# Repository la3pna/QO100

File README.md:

View this project on [CADLAB.io](https://cadlab.io/project/2009). 

# QO100
QO-100 / Eshail upconverter 2.4GHz.

Please use the cadlab link above to see the PCB and schematics.

# todo
Commit interdigital filter design
Preformance data
Graphs
LO design

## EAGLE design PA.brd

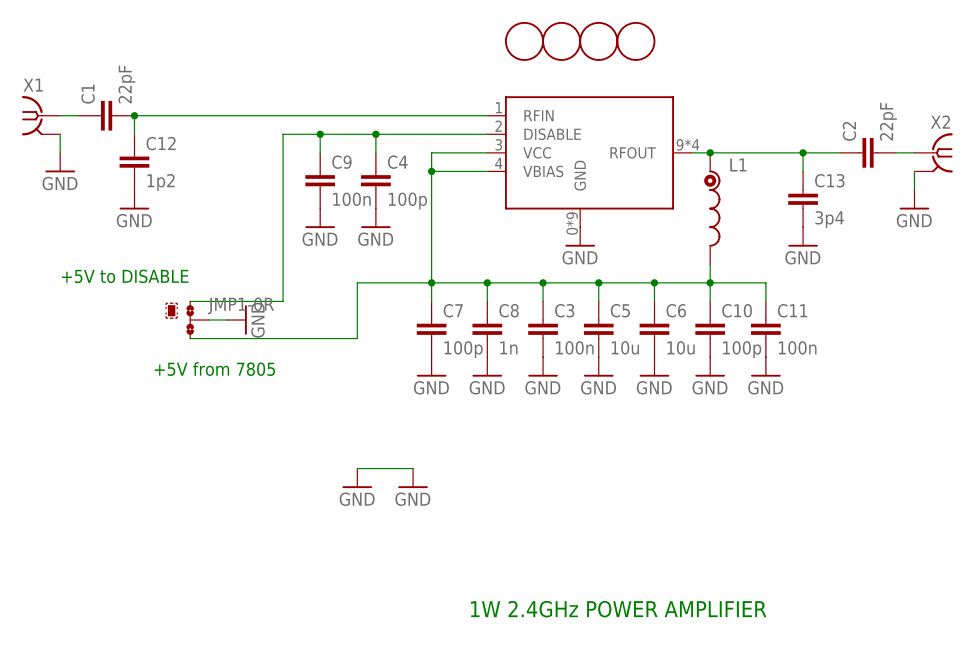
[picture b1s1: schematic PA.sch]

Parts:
C1, C2: 22pF; C0603
C3, C9, C11: 100n; C0603
C4, C7, C10: 100p; C0603
C5, C6: 10u; C1210
C8: 1n; C0603
C12: 1p2; C0603
C13: 3p4; C0603
JMP1: 0R-JUMPB; B0R-JMP
L1: INDUCTOR0603; 0603
U$1: ADL5606; LFCSP-16-4X4
U$2, U$3, U$4, U$5: FIDUCIAL; FIDUCIAL_1MM
X1, X2: SMA-142-0711-821/826; J502-ND-142-0711-821/826

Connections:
GND: C3.2, C4.2, C5.2, C6.2, C7.2, C8.2, C9.2, C10.2, C11.2, C12.2, C13.2, JMP1.2, U$1.0 (GND), U$1.5 (GND), U$1.6 (GND), U$1.7 (GND), U$1.8 (GND), U$1.13 (GND), U$1.14 (GND), U$1.15 (GND), U$1.16 (GND), X1.G@1 (2), X1.G@2 (2), X1.G@3 (2), X1.G@4 (2), X2.G@1 (2), X2.G@2 (2), X2.G@3 (2), X2.G@4 (2)
unnamed: C1.1, X1.1
unnamed: C2.1, C13.1, L1.1, U$1.9 (RFOUT), U$1.10 (RFOUT), U$1.11 (RFOUT), U$1.12 (RFOUT)
unnamed: C4.1, C9.1, JMP1.1, U$1.2 (DISABLE)
unnamed: C3.1, C5.1, C6.1, C7.1, C8.1, C10.1, C11.1, JMP1.3, L1.2, U$1.3 (VCC), U$1.4 (VBIAS)
unnamed: C2.2, X2.1
unnamed: C1.2, C12.1, U$1.1 (RFIN)

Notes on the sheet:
+5V from 7805
+5V to DISABLE
1W 2.4GHz POWER AMPLIFIER

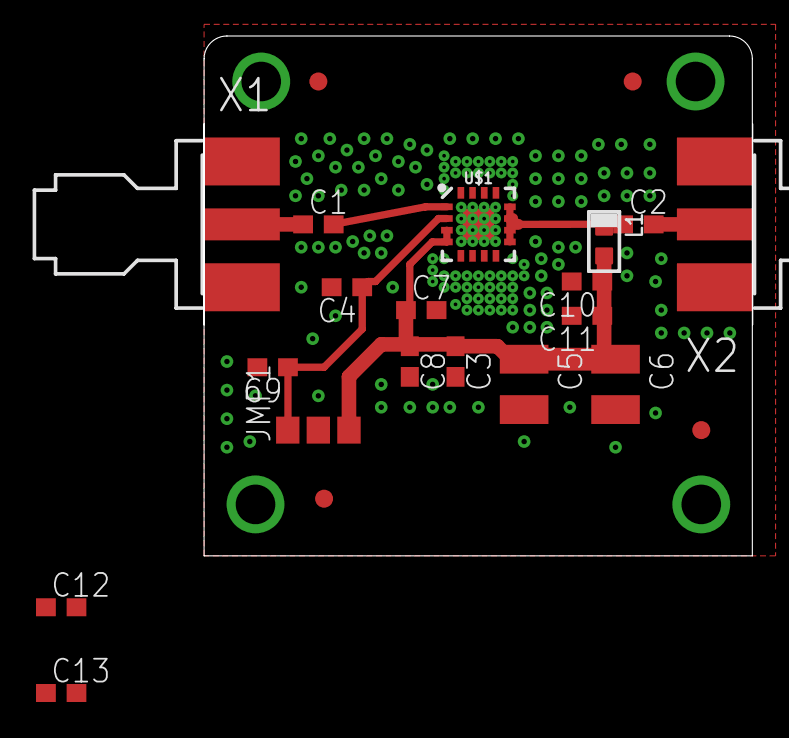
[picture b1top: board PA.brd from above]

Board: 2 copper layers, 30.5 x 28.9 mm, 22 parts (0 on the bottom side), 7 nets.

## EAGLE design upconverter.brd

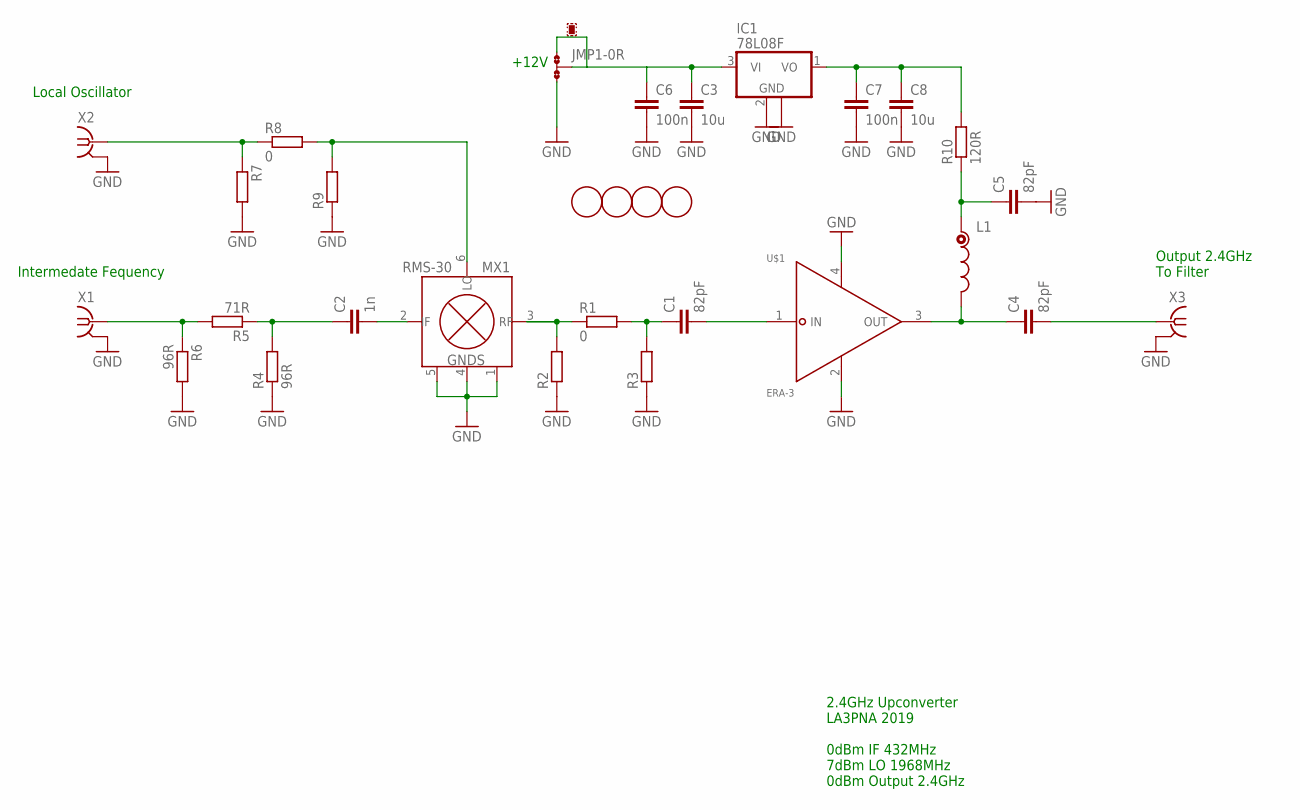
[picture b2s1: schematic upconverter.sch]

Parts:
C1, C5: 82pF; C0603K
C2: 1n; C0603K
C3, C8: 10u; C1210
C4: 82pF; C0805
C6, C7: 100n; C0603K
IC1: 78L08F; SOT89
JMP1: 0R-JUMPA; A0R-JMP
L1: INDUCTOR0603; 0603
MX1: RMS-30; CD636
R1, R8: 0; R1005
R2, R3, R7, R9: R-EU_R1005; R1005
R4, R6: 96R; R1005
R5: 71R; R1005
R10: 120R; R1206
U$1: ERA-3; MAR4SM
U$2, U$3, U$4, U$5: FIDUCIAL; FIDUCIAL_1MM
X1, X2, X3: SMA-142-0711-821/826; J502-ND-142-0711-821/826

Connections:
GND: C3.2, C5.2, C6.2, C7.2, C8.2, IC1.2 (GND), IC1.2@1 (GND), JMP1.3, MX1.1 (GND), MX1.4 (GND), MX1.5 (GND), R2.1, R3.1, R4.1, R6.2, R7.2, R9.1, U$1.2, U$1.4, X1.G@1 (2), X1.G@2 (2), X1.G@3 (2), X1.G@4 (2), X2.G@1 (2), X2.G@2 (2), X2.G@3 (2), X2.G@4 (2), X3.G@1 (2), X3.G@2 (2), X3.G@3 (2), X3.G@4 (2)
unnamed: C2.1, R4.2, R5.1
unnamed: R5.2, R6.1, X1.1
unnamed: C2.2, MX1.2 (IF)
unnamed: C4.1, L1.2, U$1.3 (OUT)
unnamed: C1.2, U$1.1 (IN)
unnamed: C1.1, R1.2, R3.2
unnamed: MX1.3 (RF), R1.1, R2.2
unnamed: R7.1, R8.1, X2.1
unnamed: MX1.6 (LO), R8.2, R9.2
unnamed: C5.1, L1.1, R10.1
unnamed: C4.2, X3.1
unnamed: C7.1, C8.1, IC1.1 (VO), R10.2
unnamed: C3.1, C6.1, IC1.3 (VI), JMP1.1, JMP1.2

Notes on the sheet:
+12V
2.4GHz Upconverter LA3PNA 2019 0dBm IF 432MHz 7dBm LO 1968MHz 0dBm Output 2.4GHz
Local Oscillator
Intermedate Fequency
Output 2.4GHz To Filter

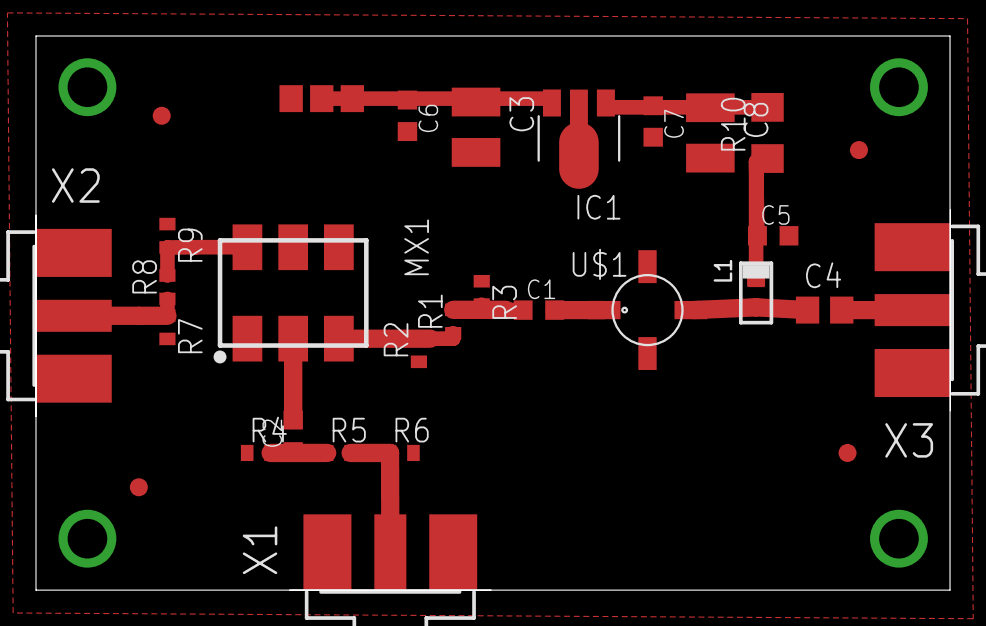
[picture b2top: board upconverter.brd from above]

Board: 2 copper layers, 50.8 x 30.8 mm, 30 parts (0 on the bottom side), 14 nets.

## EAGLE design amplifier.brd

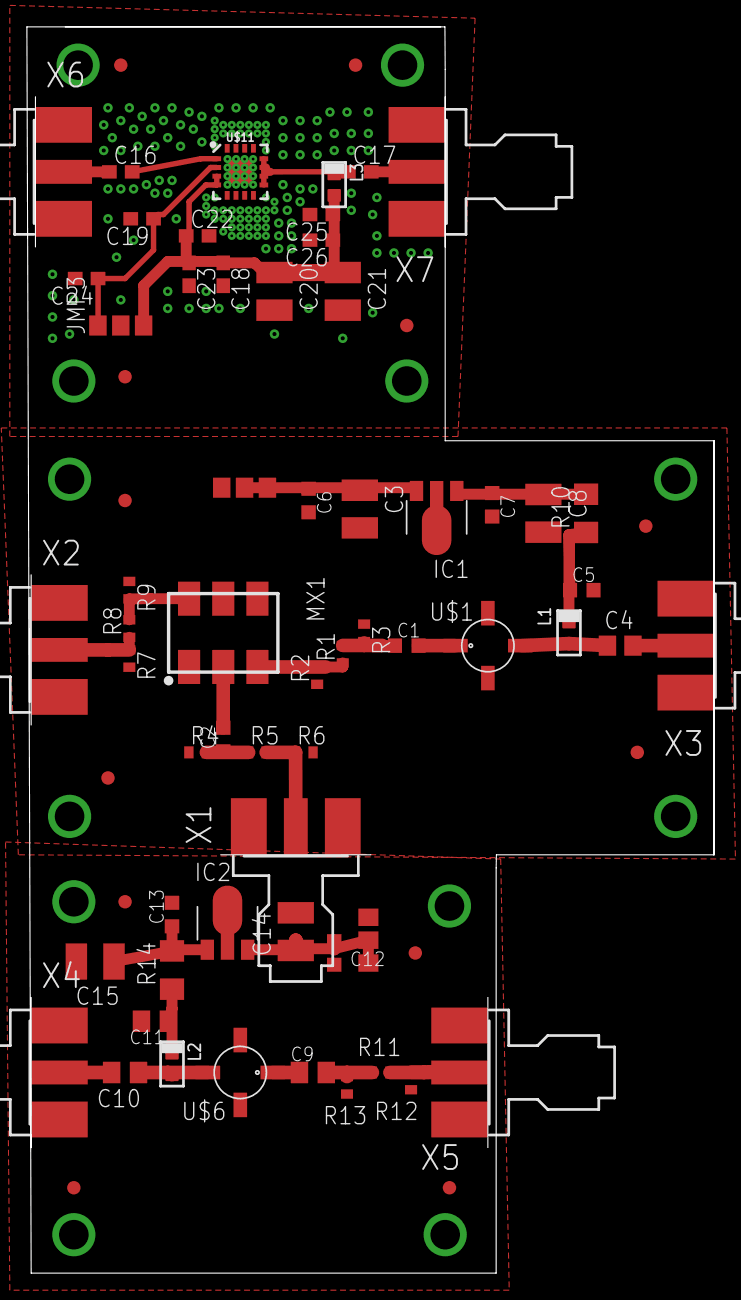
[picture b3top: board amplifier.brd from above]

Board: 2 copper layers, 51.1 x 92.7 mm, 71 parts (0 on the bottom side), 30 nets.

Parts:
C1, C2, C5, C6, C7, C12, C13: C0603K
C3, C8, C14, C15: C1210
C4: C0805
C9, C10, C11: C0805K
C16, C17: C0603
C18, C24, C26: 100n; C0603
C19, C22, C25: 100p; C0603
C20, C21: 10u; C1210
C23: 1n; C0603
IC1, IC2: 78L08F; SOT89
JMP1, JMP2: 0R-JUMPA; A0R-JMP
JMP3: 0R-JUMPB; B0R-JMP
L1, L2, L3: 0603
MX1: ADE-1; CD636
R1, R2, R3, R4, R5, R6, R7, R8, R9, R11, R12, R13: R1005
R10, R14: R1206
U$1, U$6: ERA; MAR4SM
U$2, U$3, U$4, U$5, U$7, U$8, U$9, U$10, U$12, U$13, U$14, U$15: FIDUCIAL; FIDUCIAL_1MM
U$11: ADL5606; LFCSP-16-4X4
X1, X2, X3, X4, X5, X6, X7: J502-ND-142-0711-821/826

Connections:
GND: C11.2, C12.2, C13.2, C14.2, C15.2, IC2.2, IC2.2@1, JMP2.3, R12.1, R13.1, U$6.2, U$6.4, X4.G@1, X4.G@2, X4.G@3, X4.G@4, X5.G@1, X5.G@2, X5.G@3, X5.G@4
GND1: C3.2, C5.2, C6.2, C7.2, C8.2, IC1.2, IC1.2@1, JMP1.3, MX1.1, MX1.4, MX1.5, R2.1, R3.1, R4.1, R6.2, R7.2, R9.1, U$1.2, U$1.4, X1.G@1, X1.G@2, X1.G@3, X1.G@4, X2.G@1, X2.G@2, X2.G@3, X2.G@4, X3.G@1, X3.G@2, X3.G@3, X3.G@4
GND2: C18.2, C19.2, C20.2, C21.2, C22.2, C23.2, C24.2, C25.2, C26.2, JMP3.2, U$11.0, U$11.5, U$11.6, U$11.7, U$11.8, U$11.13, U$11.14, U$11.15, U$11.16, X6.G@1, X6.G@2, X6.G@3, X6.G@4, X7.G@1, X7.G@2, X7.G@3, X7.G@4
unnamed: C2.1, R4.2, R5.1
unnamed: R5.2, R6.1, X1.1
unnamed: C2.2, MX1.2
unnamed: C4.1, L1.2, U$1.3
unnamed: C1.2, U$1.1
unnamed: C1.1, R1.2, R3.2
unnamed: MX1.3, R1.1, R2.2
unnamed: R7.1, R8.1, X2.1
unnamed: MX1.6, R8.2, R9.2
unnamed: C5.1, L1.1, R10.1
unnamed: C4.2, X3.1
unnamed: C7.1, C8.1, IC1.1, R10.2
unnamed: C3.1, C6.1, IC1.3, JMP1.1, JMP1.2
unnamed: C10.1, L2.2, U$6.3
unnamed: C9.2, U$6.1
unnamed: C9.1, R11.2, R13.2
unnamed: R11.1, R12.2, X5.1
unnamed: C11.1, L2.1, R14.1
unnamed: C10.2, X4.1
unnamed: C13.1, C15.1, IC2.1, R14.2
unnamed: C12.1, C14.1, IC2.3, JMP2.1, JMP2.2
unnamed: C19.1, C24.1, JMP3.1, U$11.2
unnamed: C18.1, C20.1, C21.1, C22.1, C23.1, C25.1, C26.1, JMP3.3, L3.2, U$11.3, U$11.4
unnamed: C16.1, X6.1
unnamed: C17.1, L3.1, U$11.9, U$11.10, U$11.11, U$11.12
unnamed: C17.2, X7.1
unnamed: C16.2, U$11.1

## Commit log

2019-07-29 Backlink to CADLAB.io has been added.
2019-07-29 PCB files
